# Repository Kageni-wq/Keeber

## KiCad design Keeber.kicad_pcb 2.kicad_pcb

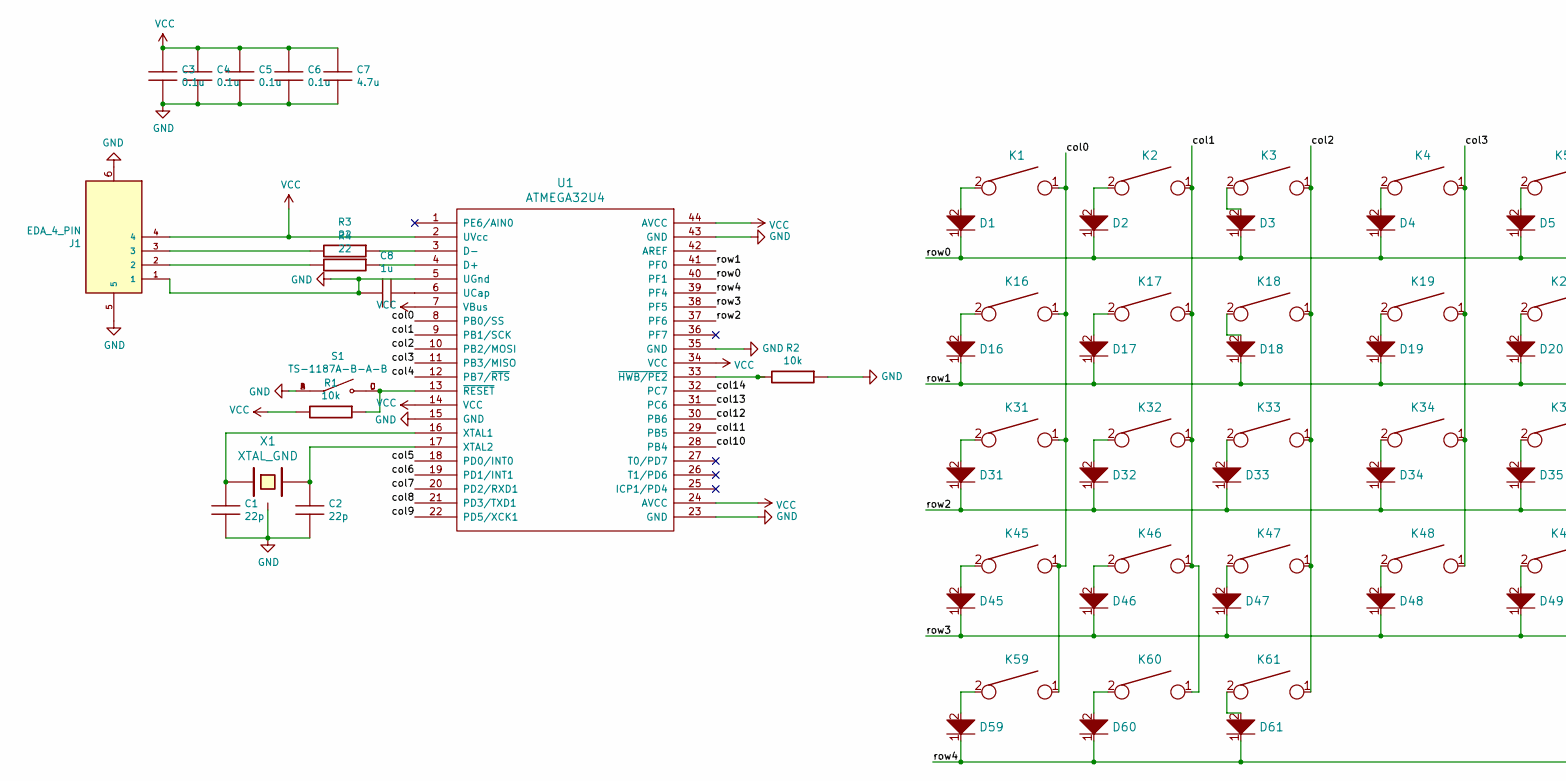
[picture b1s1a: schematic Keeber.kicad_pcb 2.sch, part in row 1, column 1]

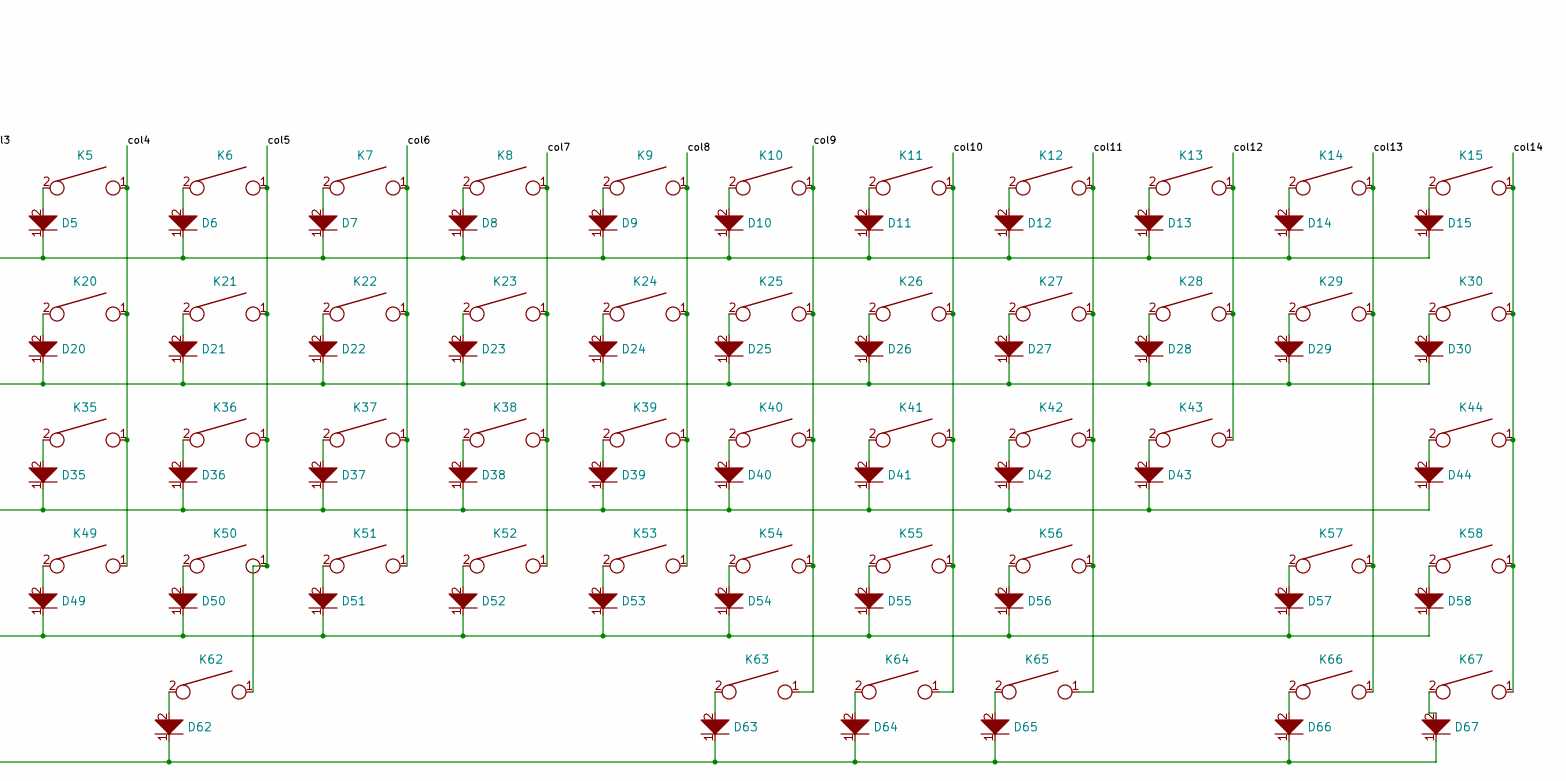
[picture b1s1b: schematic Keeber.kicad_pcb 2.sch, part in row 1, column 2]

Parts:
C1, C2: 22p; C_0805_2012Metric_Pad1.18x1.45mm_HandSolder
C3, C4, C5, C6: 0.1u; C_0805_2012Metric_Pad1.18x1.45mm_HandSolder
C7: 4.7u; C_0805_2012Metric_Pad1.18x1.45mm_HandSolder
C8: 1u; C_0805_2012Metric_Pad1.18x1.45mm_HandSolder
D1, D2, D3, D4, D5, D6, D7, D8, D9, D10, D11, D12, D13, D14, D15, D16, D17, D18, D19, D20, D21, D22, D23, D24, D25, D26, D27, D28, D29, D30, D31, D32, D33, D34, D35, D36, D37, D38, D39, D40, D41, D42, D43, D44, D45, D46, D47, D48, D49, D50, D51, D52, D53, D54, D55, D56, D57, D58, D59, D60, D61, D62, D63, D64, D65, D66, D67: D; D_SOD123_axial
J1: EDA_4_PIN; EDA4PIN
K1, K2, K3, K4, K5, K6, K7, K8, K9, K10, K11, K12, K13, K15, K17, K18, K19, K20, K21, K22, K23, K24, K25, K26, K27, K28, K30, K32, K33, K34, K35, K36, K37, K38, K39, K40, K41, K42, K44, K46, K47, K48, K49, K50, K51, K52, K53, K54, K55, K57, K58, K65, K66, K67: KEYSW; SW_Cherry_MX_1.00u_PCB
K14: KEYSW; SW_Cherry_MX_2.00u_PCB
K16, K29: KEYSW; SW_Cherry_MX_1.50u_PCB
K31, K56: KEYSW; SW_Cherry_MX_1.75u_PCB
K43, K45: KEYSW; SW_Cherry_MX_2.25u_PCB
K59, K60, K61, K63, K64: KEYSW; SW_Cherry_MX_1.25u_PCB
K62: KEYSW; SW_Cherry_MX_6.25u_PCB
R1, R2: 10k; R_0805_2012Metric_Pad1.20x1.40mm_HandSolder
R3, R4: 22; R_0805_2012Metric_Pad1.20x1.40mm_HandSolder
S1: TS-1187A-B-A-B; SW_TS-1187A-B-A-B; PARTREV A0
U1: ATMEGA32U4; QFN44G-0.5-7X7MM
X1: XTAL_GND; Crystal_SMD_SeikoEpson_FA238-4Pin_3.2x2.5mm_HandSoldering

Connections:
/col0: K1.1, K16.1, K31.1, K45.1, K59.1, U1.8 (PB0/SS)
/col1: K2.1, K17.1, K32.1, K46.1, K60.1, U1.9 (PB1/SCK)
/col2: K3.1, K18.1, K33.1, K47.1, K61.1, U1.10 (PB2/MOSI)
/col3: K4.1, K19.1, K34.1, K48.1, U1.11 (PB3/MISO)
/col4: K5.1, K20.1, K35.1, K49.1, U1.12 (PB7/~RTS)
/col5: K6.1, K21.1, K36.1, K50.1, K62.1, U1.18 (PD0/INT0)
/col6: K7.1, K22.1, K37.1, K51.1, U1.19 (PD1/INT1)
/col7: K8.1, K23.1, K38.1, K52.1, U1.20 (PD2/RXD1)
/col8: K9.1, K24.1, K39.1, K53.1, U1.21 (PD3/TXD1)
/col9: K10.1, K25.1, K40.1, K54.1, K63.1, U1.22 (PD5/XCK1)
/col10: K11.1, K26.1, K41.1, K55.1, K64.1, U1.28 (PB4)
/col11: K12.1, K27.1, K42.1, K56.1, K65.1, U1.29 (PB5)
/col12: K13.1, K28.1, K43.1, U1.30 (PB6)
/col13: K14.1, K29.1, K57.1, K66.1, U1.31 (PC6)
/col14: K15.1, K30.1, K44.1, K58.1, K67.1, U1.32 (PC7)
/row0: D1.1, D2.1, D3.1, D4.1, D5.1, D6.1, D7.1, D8.1, D9.1, D10.1, D11.1, D12.1, D13.1, D14.1, D15.1, U1.40 (PF1)
/row1: D16.1, D17.1, D18.1, D19.1, D20.1, D21.1, D22.1, D23.1, D24.1, D25.1, D26.1, D27.1, D28.1, D29.1, D30.1, U1.41 (PF0)
/row2: D31.1, D32.1, D33.1, D34.1, D35.1, D36.1, D37.1, D38.1, D39.1, D40.1, D41.1, D42.1, D43.1, D44.1, U1.37 (PF6)
/row3: D45.1, D46.1, D47.1, D48.1, D49.1, D50.1, D51.1, D52.1, D53.1, D54.1, D55.1, D56.1, D57.1, D58.1, U1.38 (PF5)
/row4: D59.1, D60.1, D61.1, D62.1, D63.1, D64.1, D65.1, D66.1, D67.1, U1.39 (PF4)
GND: C1.2, C2.2, C3.2, C4.2, C5.2, C6.2, C7.2, C8.2, J1.1, J1.5, J1.6, R2.1, S1.A, S1.B, U1.5 (UGnd), U1.15 (GND), U1.23 (GND), U1.35 (GND), U1.43 (GND), X1.3
unnamed: C1.1, U1.16 (XTAL1), X1.1
unnamed: C2.1, U1.17 (XTAL2), X1.2
unnamed: C8.1, U1.6 (UCap)
unnamed: D1.2, K1.2
unnamed: D2.2, K2.2
unnamed: D3.2, K3.2
unnamed: D4.2, K4.2
unnamed: D5.2, K5.2
unnamed: D6.2, K6.2
unnamed: D7.2, K7.2
unnamed: D8.2, K8.2
unnamed: D9.2, K9.2
unnamed: D10.2, K10.2
unnamed: D11.2, K11.2
unnamed: D12.2, K12.2
unnamed: D13.2, K13.2
unnamed: D14.2, K14.2
unnamed: D15.2, K15.2
unnamed: D16.2, K16.2
unnamed: D17.2, K17.2
unnamed: D18.2, K18.2
unnamed: D19.2, K19.2
unnamed: D20.2, K20.2
unnamed: D21.2, K21.2
unnamed: D22.2, K22.2
unnamed: D23.2, K23.2
unnamed: D24.2, K24.2
unnamed: D25.2, K25.2
unnamed: D26.2, K26.2
unnamed: D27.2, K27.2
unnamed: D28.2, K28.2
unnamed: D29.2, K29.2
unnamed: D30.2, K30.2
unnamed: D31.2, K31.2
unnamed: D32.2, K32.2
unnamed: D33.2, K33.2
unnamed: D34.2, K34.2
unnamed: D35.2, K35.2
unnamed: D36.2, K36.2
unnamed: D37.2, K37.2
unnamed: D38.2, K38.2
unnamed: D39.2, K39.2
unnamed: D40.2, K40.2
unnamed: D41.2, K41.2
unnamed: D42.2, K42.2
unnamed: D43.2, K43.2
unnamed: D44.2, K44.2
unnamed: D45.2, K45.2
unnamed: D46.2, K46.2
unnamed: D47.2, K47.2
unnamed: D48.2, K48.2
unnamed: D49.2, K49.2
unnamed: D50.2, K50.2
unnamed: D51.2, K51.2
unnamed: D52.2, K52.2
unnamed: D53.2, K53.2
unnamed: D54.2, K54.2
unnamed: D55.2, K55.2
unnamed: D56.2, K56.2
unnamed: D57.2, K57.2
unnamed: D58.2, K58.2
unnamed: D59.2, K59.2
unnamed: D60.2, K60.2
unnamed: D61.2, K61.2
unnamed: D62.2, K62.2
unnamed: D63.2, K63.2
unnamed: D64.2, K64.2
unnamed: D65.2, K65.2
unnamed: D66.2, K66.2
unnamed: D67.2, K67.2
unnamed: J1.2, R4.2
unnamed: J1.3, R3.2
unnamed: R1.1, S1.C, S1.D, U1.13 (~RESET)
unnamed: R2.2, U1.33 (~HWB/PE2)
unnamed: R3.1, U1.3 (D-)
unnamed: R4.1, U1.4 (D+)
VCC: C3.1, C4.1, C5.1, C6.1, C7.1, J1.4, R1.2, U1.2 (UVcc), U1.7 (VBus), U1.14 (VCC), U1.24 (AVCC), U1.34 (VCC), U1.44 (AVCC)

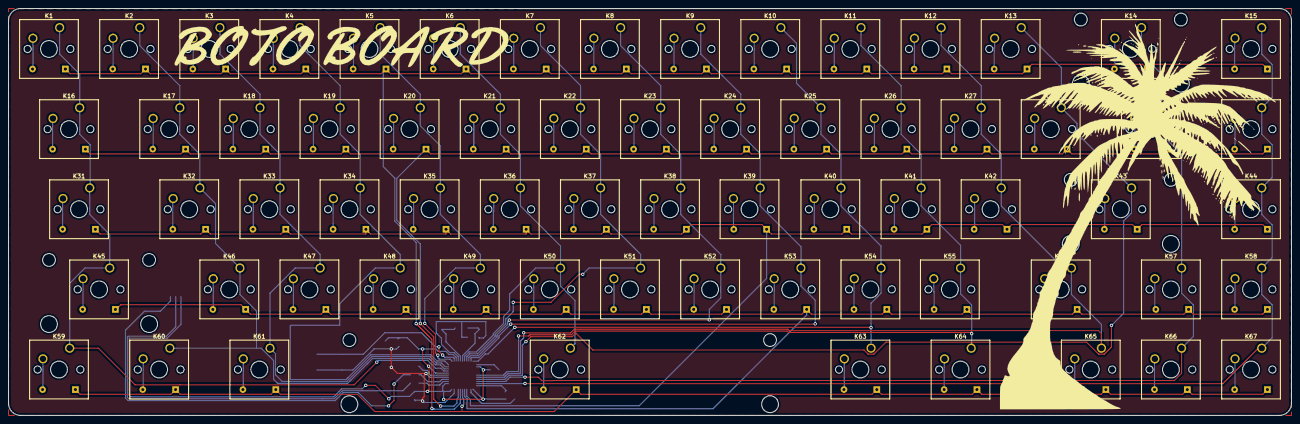
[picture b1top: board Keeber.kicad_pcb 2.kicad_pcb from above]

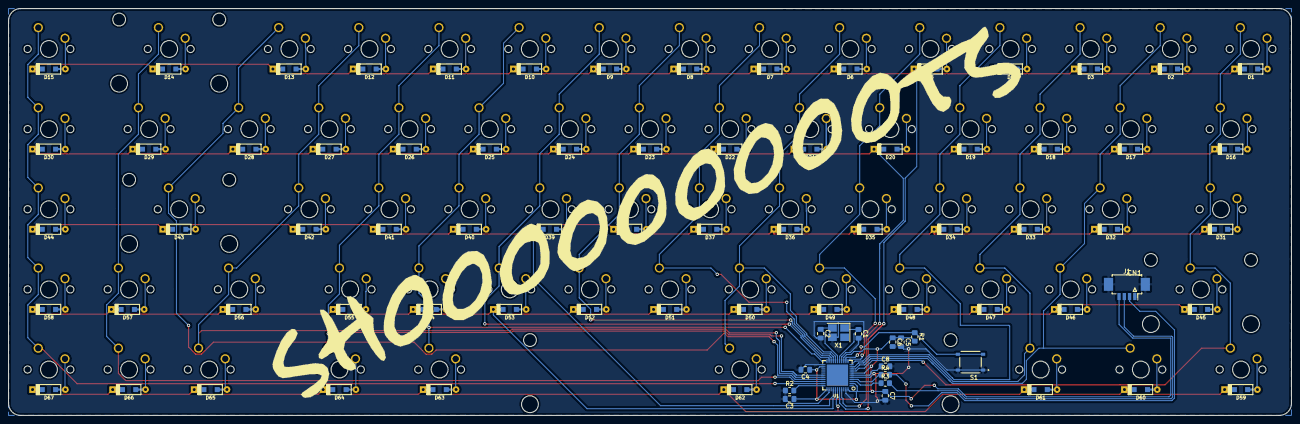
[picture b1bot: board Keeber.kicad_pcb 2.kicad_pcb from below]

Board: 2 copper layers, 305.0 x 96.7 mm, 150 parts (83 on the bottom side), 98 nets.
